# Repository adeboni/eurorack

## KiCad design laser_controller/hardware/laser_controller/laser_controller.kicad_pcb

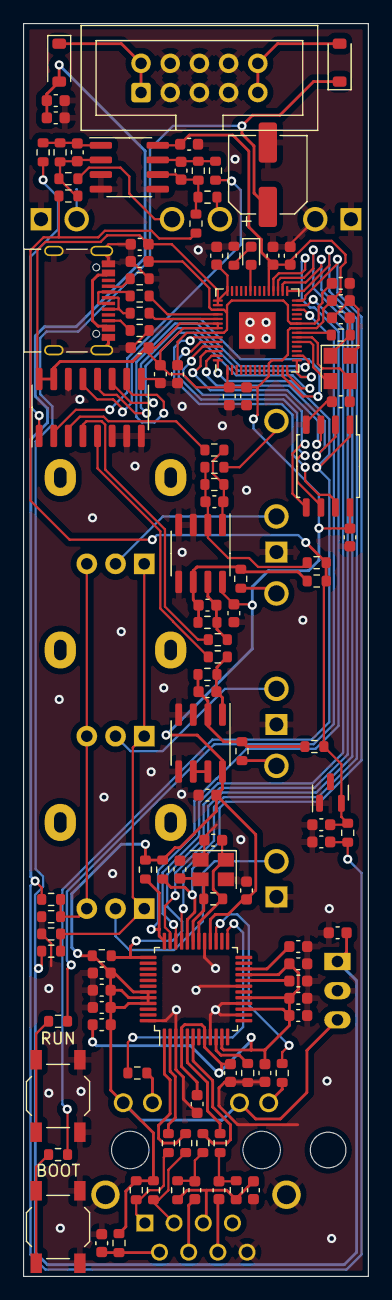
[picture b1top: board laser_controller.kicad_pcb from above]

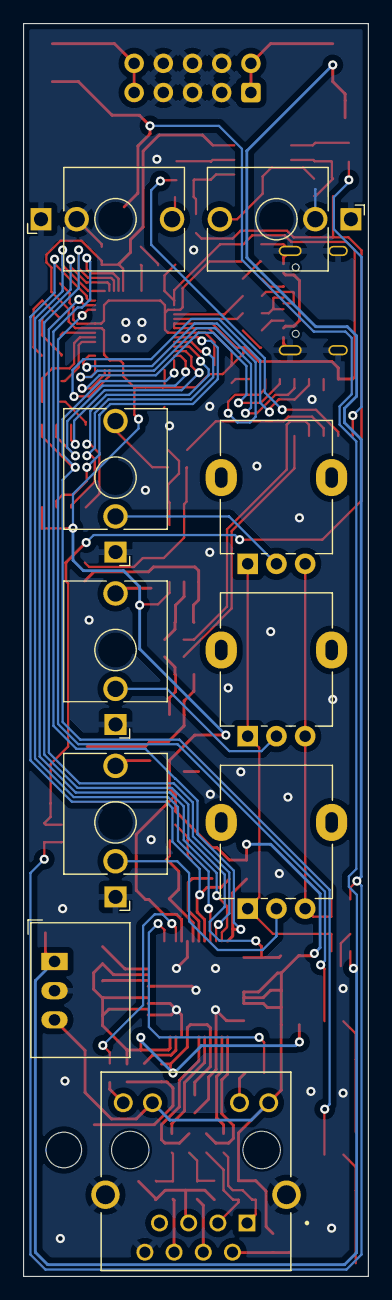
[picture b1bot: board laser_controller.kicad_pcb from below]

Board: 2 copper layers, 30.0 x 109.0 mm, 124 parts (10 on the bottom side), 87 nets.

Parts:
C1, C2, C3, C4, C5, C6, C7, C8, C9, C12, C13, C14, C15, C16, C17, C18, C19, C20, C21, C24, C29, C32, C33, C36, C37: 100n; C_0603_1608Metric
C10, C11, C47, C48: 1u; C_0603_1608Metric
C22, C25: 27p; C_0603_1608Metric
C23, C26: 18p; C_0603_1608Metric
C27: 4.7u; C_0603_1608Metric
C28: 22n; C_0603_1608Metric
C30, C31: 6.8n; C_0603_1608Metric
C34, C35, C44, C45: 10u; C_0603_1608Metric
C38, C39, C40, C41, C42: 470p; C_0603_1608Metric
C49: 100u; CP_Elec_6.3x5.4
D1: LED; LED_0603_1608Metric
D3, D5: SM4007; D_SOD-123
FB1: FerriteBead; L_0603_1608Metric
J1, J2, J3, J4, J5: AudioJack2_SwitchT; Jack_3.5mm_QingPu_WQP-PJ398SM_Vertical_CircularHoles
J6: Conn_02x05_Odd_Even; IDC-Header_2x05_P2.54mm_Vertical
J14: USB_C_Receptacle_USB2.0; USB_C_Receptacle_Palconn_UTC16-G
J16: SI-46001-F; BEL_SI-46001-F
R1, R4, R6, R7, R10, R11, R14, R15, R18, R19: 100k; R_0603_1608Metric
R2, R5, R9, R13, R17: 75k; R_0603_1608Metric
R3, R8, R12, R16, R20: 27k; R_0603_1608Metric
R21: 2k; R_0603_1608Metric
R22, R24, R52, R57, R59: 4.7k; R_0603_1608Metric
R23, R25: 3.3k; R_0603_1608Metric
R45, R46: 27; R_0603_1608Metric
R51, R54: 5.1k; R_0603_1608Metric
R53, R55, R56, R58: 4.7; R_0603_1608Metric
R60, R61, R62, R63: 49.9; R_0603_1608Metric
R68: 1M; R_0603_1608Metric
R69, R73, R77, R78: 1k; R_0603_1608Metric
R70, R71: 470; R_0603_1608Metric
R72: 10; R_0603_1608Metric
R74: 12.4k; R_0603_1608Metric
RV1, RV2, RV3: 1M; Potentiometer_Alpha_RD901F-40-00D_Single_Vertical
SW2, SW3: SW_Push; SW_SPST_TL3342
U1: MCP3208; SOIC-16_3.9x9.9mm_P1.27mm
U2, U3, U8: MCP6002-xSN; SOIC-8_3.9x4.9mm_P1.27mm
U4: RP2040; QFN-56-1EP_7x7mm_P0.4mm_EP3.2x3.2mm
U5: W5500; LQFP-48_7x7mm_P0.5mm
U7: W25Q128JVS; SOIC-8_5.23x5.23mm_P1.27mm
U9: LM4040-5V; SOT-23
U10: R-783.3-1.0; Converter_DCDC_RECOM_R-78E-0.5_THT
Y1: 12MHz; Crystal_SMD_3225-4Pin_3.2x2.5mm
Y2: 25MHz; Crystal_SMD_3225-4Pin_3.2x2.5mm

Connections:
+1V1: C1.1, C2.1, C10.1, U4.23 (DVDD), U4.45 (VREG_VOUT), U4.50 (DVDD)
+3.3V: C3.1, C4.1, C5.1, C6.1, C7.1, C8.1, C9.1, C11.1, C12.1, C13.1, C14.1, C15.1, C32.1, C33.1, C35.1, C36.1, C37.1, FB1.1, J16.10, J16.12, R52.1, R57.1, R59.1, R60.2, R61.2, R72.2, U1.15 (Vref), U1.16 (Vdd), U2.8 (V+), U3.8 (V+), U4.1 (IOVDD), U4.10 (IOVDD), U4.22 (IOVDD), U4.33 (IOVDD), U4.42 (IOVDD), U4.43 (ADC_AVDD), U4.44 (VREG_IN), U4.48 (USB_VDD), U4.49 (IOVDD), U5.28 (VDD), U5.43 (PMODE2), U5.44 (PMODE1), U5.45 (PMODE0), U7.8 (VCC), U8.8 (V+), U10.3 (OUT)
+3.3VA: C16.1, C17.1, C18.1, C19.1, C20.1, C21.1, FB1.2, U5.4 (AVDD), U5.8 (AVDD), U5.11 (AVDD), U5.15 (AVDD), U5.17 (AVDD), U5.21 (AVDD)
+12V: C34.1, C49.1, D3.1 (K), R22.1, U10.1 (IN)
-12V: C44.2, C45.2, C47.1, D5.2 (A), R21.1, R24.1
/CS_0: R52.2, U4.28 (GPIO17), U5.32 (~SCS)
/GPIO16: U4.27 (GPIO16), U5.34 (MISO)
/GPIO18: U4.29 (GPIO18), U5.33 (SCLK)
/GPIO19: U4.30 (GPIO19), U5.35 (MOSI)
/GPIO20: R59.2, U4.31 (GPIO20), U5.37 (~RST)
/GPIO21: R57.2, U4.32 (GPIO21), U5.36 (~INT)
/QSPI_SCLK: U4.52 (QSPI_SCLK), U7.6 (CLK)
/QSPI_SD0: U4.53 (QSPI_SD0), U7.5 (DI(IO0))
/QSPI_SD1: U4.55 (QSPI_SD1), U7.2 (DO(IO1))
/QSPI_SD2: U4.54 (QSPI_SD2), U7.3 (IO2)
/QSPI_SD3: U4.51 (QSPI_SD3), U7.7 (IO3)
/QSPI_SS: R78.1, U4.56 (QSPI_SS), U7.1 (~CS)
/RUN: R73.1, U4.26 (RUN)
/~USB_BOOT: R78.2, SW3.2
ACTn: R71.1, U5.27 (ACTLED)
CS_1: U1.10 (~CS/SHDN), U4.16 (GPIO13)
D+: J14.A6 (D+), J14.B6 (D+), R45.1
D-: J14.A7 (D-), J14.B7 (D-), R46.1
GND: C1.2, C2.2, C3.2, C4.2, C5.2, C6.2, C7.2, C8.2, C9.2, C10.2, C11.2, C12.2, C13.2, C14.2, C15.2, C16.2, C17.2, C18.2, C19.2, C20.2, C21.2, C22.2, C23.1, C24.1, C25.2, C26.2, C27.2, C28.1, C29.2, C32.2, C33.2, C34.2, C35.2, C36.2, C37.2, C44.1, C45.1, C47.2, C48.2, C49.2, J1.S, J1.TN, J2.S, J2.TN, J3.S, J4.S, J5.S, J6.3, J6.4, J6.5, J6.6, J6.7, J6.8, J14.A1 (GND), J14.A12 (GND), J14.B1 (GND), J14.B12 (GND), J14.S1 (SHIELD), J16.8, J16.SH, R23.2, R25.2, R51.1, R54.1, R74.1, R77.2, SW2.1, SW3.1, U1.6 (CH5), U1.7 (CH6), U1.8 (CH7), U1.9 (DGND), U1.14 (AGND), U2.3 (+), U2.4 (V-), U2.5 (+), U3.3 (+), U3.4 (V-), U3.5 (+), U4.19 (TESTEN), U4.57 (GND), U5.3 (AGND), U5.9 (AGND), U5.14 (AGND), U5.16 (AGND), U5.19 (AGND), U5.29 (GND), U5.48 (AGND), U7.4 (GND), U8.3 (+), U8.4 (V-), U8.5 (+), U9.1 (K), U10.2 (GND), Y1.2, Y1.4, Y2.2, Y2.4
LINKn: R70.1, U5.25 (LINKLED)
MISO_1: U1.12 (Dout), U4.15 (GPIO12)
MOSI_1: U1.11 (Din), U4.14 (GPIO11)
unnamed: C25.1, R69.2, Y1.1
unnamed: C38.1, R3.2, R4.1, U2.1
unnamed: C39.1, R6.1, R8.2, U2.7
unnamed: C40.1, R10.1, R12.2, U3.1
unnamed: C41.1, R14.1, R16.2, U3.7
unnamed: C42.1, R18.1, R20.2, U8.1
unnamed: D1.2 (A), U4.37 (GPIO25)
unnamed: D1.1 (K), R77.1
unnamed: D3.2 (A), J6.9, J6.10
unnamed: D5.1 (K), J6.1, J6.2
unnamed: J1.T, R1.1
unnamed: J2.T, R7.1
unnamed: J3.T, R19.1
unnamed: J3.TN, RV3.2
unnamed: J4.T, R11.1
unnamed: J4.TN, RV1.2
unnamed: J5.T, R15.1
unnamed: J5.TN, RV2.2
unnamed: J14.A5 (CC1), R51.2
unnamed: J14.B5 (CC2), R54.2
unnamed: J14.A4 (VBUS), J14.A9 (VBUS), J14.B4 (VBUS), J14.B9 (VBUS)
unnamed: J16.9, R71.2
unnamed: J16.11, R70.2
unnamed: C30.2, J16.4 (RD+)
unnamed: C31.1, J16.6 (RD-)
unnamed: C28.2, J16.2 (TCT), R72.1
unnamed: R22.2, R23.1, RV1.1, RV2.1, RV3.1
unnamed: R24.2, R25.1, RV1.3, RV2.3, RV3.3
unnamed: R73.2, SW2.2
unnamed: R4.2, U1.1 (CH0)
unnamed: R6.2, U1.2 (CH1)
unnamed: R10.2, U1.3 (CH2)
unnamed: R14.2, U1.4 (CH3)
unnamed: R18.2, U1.5 (CH4)
unnamed: C38.2, R1.2, R2.1, R3.1, U2.2 (-)
unnamed: C39.2, R5.1, R7.2, R8.1, U2.6 (-)
unnamed: C40.2, R9.1, R11.2, R12.1, U3.2 (-)
unnamed: C41.2, R13.1, R15.2, R16.1, U3.6 (-)
unnamed: R46.2, U4.46 (USB_DM)
unnamed: R45.2, U4.47 (USB_DP)
unnamed: C22.1, U4.20 (XIN), Y1.3
unnamed: R69.1, U4.21 (XOUT)
unnamed: C29.1, U5.22 (1V2O)
unnamed: R74.2, U5.10 (EXRES1)
unnamed: R56.1, U5.5 (RXN)
unnamed: R58.2, U5.6 (RXP)
unnamed: C27.1, U5.20 (TOCAP)
unnamed: R53.1, U5.1 (TXN)
unnamed: R55.2, U5.2 (TXP)
unnamed: C23.2, R68.2, U5.30 (XI/CLKIN), Y2.1
unnamed: C26.1, R68.1, U5.31 (XO), Y2.3
unnamed: C42.2, R17.1, R19.2, R20.1, U8.2 (-)
unnamed: U8.6 (-), U8.7
RCT: C24.2, J16.5 (RCT), R62.2, R63.2
RXN: C31.2, R56.2, R62.1
RXP: C30.1, R58.1, R63.1
SCK_1: U1.13 (CLK), U4.13 (GPIO10)
TXN: J16.3 (TD-), R53.2, R60.1
TXP: J16.1 (TD+), R55.1, R61.1
VREF-5V: C48.1, R2.2, R5.2, R9.2, R13.2, R17.2, R21.2, U9.2 (A)

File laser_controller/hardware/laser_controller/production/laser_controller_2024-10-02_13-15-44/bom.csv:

Designator,Footprint,Quantity,Value,LCSC Part #
"C1, C12, C13, C14, C15, C16, C17, C18, C19, C2, C20, C21, C24, C29, C3, C32, C33, C36, C37, C4, C5, C6, C7, C8, C9",0603,25,100n,C14663
"C10, C11, C47, C48",0603,4,1u,C15849
"C22, C25",0603,2,27p,C107045
"C23, C26",0603,2,18p,C1647
C27,0603,1,4.7u,C19666
C28,0603,1,22n,C21122
"C30, C31",0603,2,6.8n,C1631
"C34, C35, C43, C44, C45, C46",0603,6,10u,C96446
"C38, C39, C40, C41, C42",0603,5,470p,C1620
D1,0603,1,LED,C2286
"D3, D5",D_SOD-123,2,SM4007,C64898
FB1,0603,1,FerriteBead,C1002
J14,USB_C_Receptacle_Palconn_UTC16-G,1,USB_C_Receptacle_USB2.0,C709357
"R1, R10, R11, R14, R15, R18, R19, R4, R6, R7",0603,10,100k,C25803
"R12, R16, R20, R3, R8",0603,5,27k,C22967
"R13, R17, R2, R5, R9",0603,5,75k,C23242
R21,0603,1,2k,C22975
"R22, R24, R52, R57, R59",0603,5,4.7k,C23162
"R23, R25",0603,2,3.3k,C22978
"R45, R46",0603,2,27,C25190
"R51, R54",0603,2,5.1k,C23186
"R53, R55, R56, R58",0603,4,4.7,C23164
"R60, R61, R62, R63",0603,4,49.9,C23185
R68,0603,1,1M,C22935
"R69, R73, R77, R78",0603,4,1k,C21190
"R70, R71",0603,2,470,C23179
R72,0603,1,10,C22859
R74,0603,1,12.4k,C22865
"SW2, SW3",SW_SPST_TL3342,2,SW_Push,C318884
U1,SOIC-16_3.9x9.9mm_P1.27mm,1,MCP3208,C16939
"U2, U3, U8",SOIC-8_3.9x4.9mm_P1.27mm,3,MCP6002-xSN,C7377
U4,QFN-56-1EP_7x7mm_P0.4mm_EP3.2x3.2mm,1,RP2040,C2040
U5,LQFP-48_7x7mm_P0.5mm,1,W5500,C32843
U7,SOIC-8_5.23x5.23mm_P1.27mm,1,W25Q128JVS,C97521
U9,SOT-23,1,LM4040-5V,C206488
Y1,Crystal_SMD_3225-4Pin_3.2x2.5mm,1,12MHz,C9002
Y2,Crystal_SMD_3225-4Pin_3.2x2.5mm,1,25MHz,C9006

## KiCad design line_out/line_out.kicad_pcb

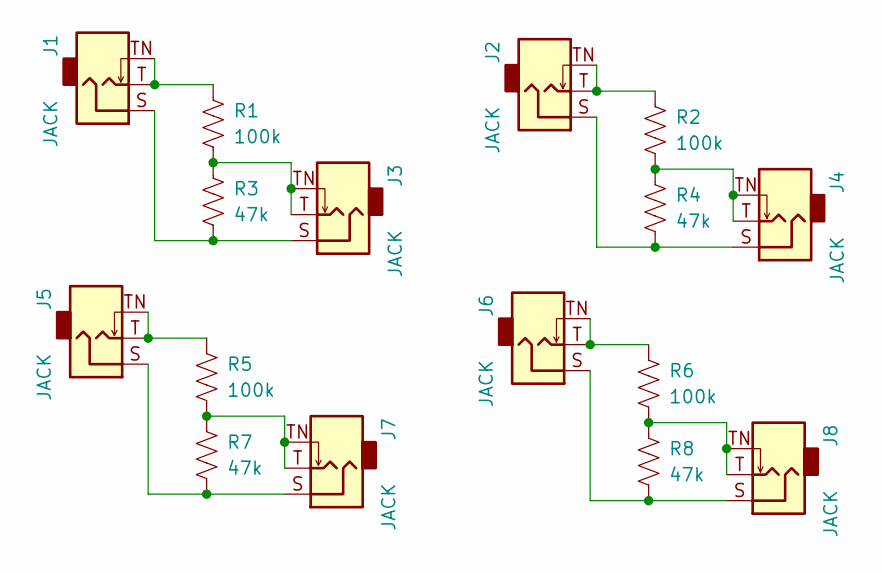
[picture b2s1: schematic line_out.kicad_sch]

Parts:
J1, J2, J3, J4, J5, J6, J7, J8: JACK; Jack_3.5mm_QingPu_WQP-PJ398SM_Vertical_CircularHoles
R1, R2, R5, R6: 100k; R_0603_1608Metric
R3, R4, R7, R8: 47k; R_0603_1608Metric

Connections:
unnamed: J1.S, J3.S, R3.2
unnamed: J1.T, J1.TN, R1.1
unnamed: J2.S, J4.S, R4.2
unnamed: J2.T, J2.TN, R2.1
unnamed: J3.T, J3.TN, R1.2, R3.1
unnamed: J4.T, J4.TN, R2.2, R4.1
unnamed: J5.S, J7.S, R7.2
unnamed: J5.T, J5.TN, R5.1
unnamed: J6.S, J8.S, R8.2
unnamed: J6.T, J6.TN, R6.1
unnamed: J7.T, J7.TN, R5.2, R7.1
unnamed: J8.T, J8.TN, R6.2, R8.1

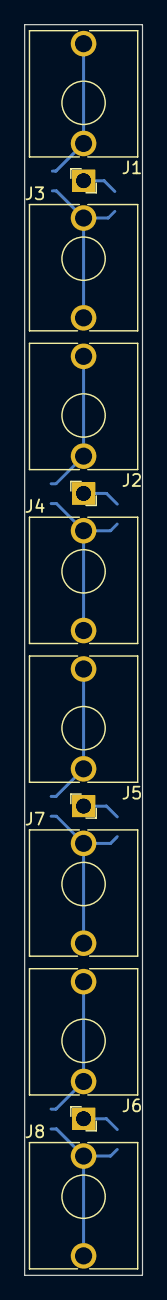
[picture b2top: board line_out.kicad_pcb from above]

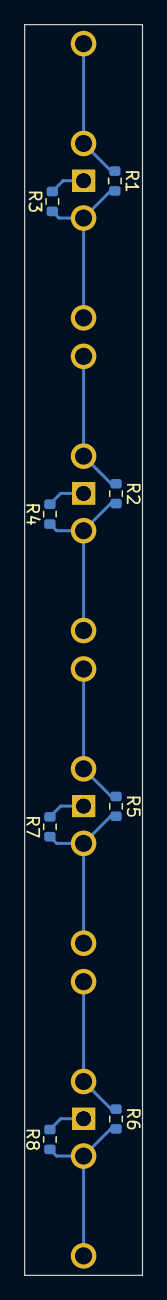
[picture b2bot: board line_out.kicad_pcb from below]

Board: 2 copper layers, 9.8 x 104.0 mm, 16 parts (8 on the bottom side), 12 nets.

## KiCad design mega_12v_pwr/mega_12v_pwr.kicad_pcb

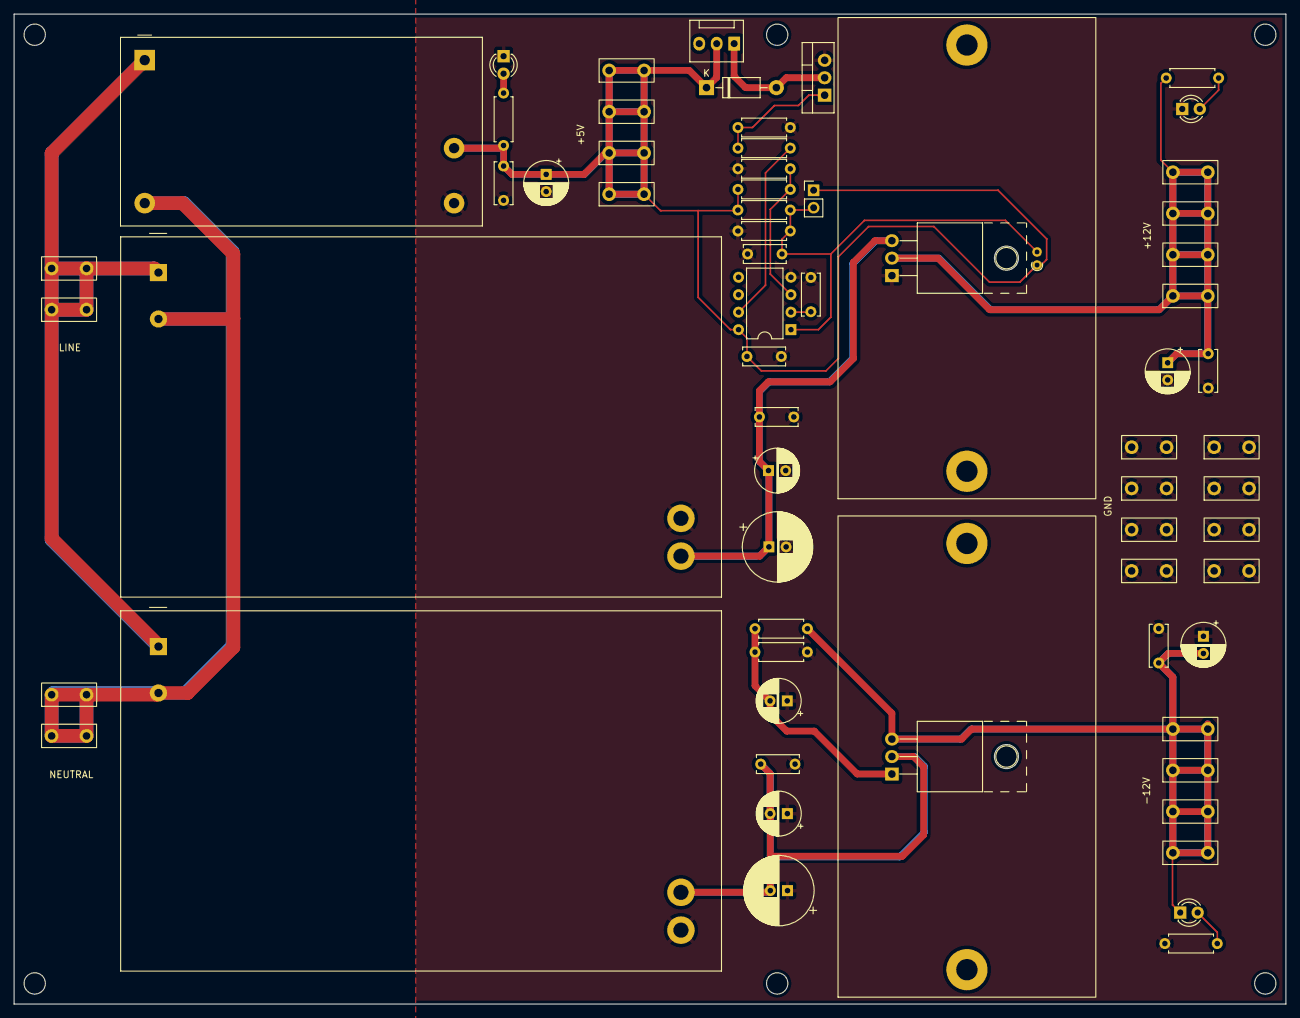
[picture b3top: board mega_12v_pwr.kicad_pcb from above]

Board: 2 copper layers, 185.0 x 144.0 mm, 67 parts (0 on the bottom side), 18 nets.

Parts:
C1, C2, C3, C4, C5, C8: 10u; CP_Radial_D6.3mm_P2.50mm
C6, C7: 100u; CP_Radial_D10.0mm_P2.50mm
C9, C10, C11, C12, C13, C14: 100n; C_Disc_D6.0mm_W2.5mm_P5.00mm
C15: 1u; C_Disc_D6.0mm_W2.5mm_P5.00mm
C17: 10n; C_Disc_D6.0mm_W2.5mm_P5.00mm
D1, D2, D3: LED; LED_D3.0mm
D4: 1N4007; D_DO-41_SOD81_P10.16mm_Horizontal
HS1, HS2: Heatsink; SK64
J1, J2, J3, J4, J5, J6, J7, J8, J9, J10, J11, J12, J13, J14, J15, J16, J17, J18, J19, J20, J22, J23, J24, J25: Conn_01x01; SPADE
J21: Conn_01x02; PinHeader_1x02_P2.54mm_Vertical
M1: Fan_PC_Chassis; FanPinHeader_1x03_P2.54mm_Vertical
PS1: IRM-20-5; Converter_ACDC_MeanWell_IRM-20-xx_THT
PS2, PS3: IRM-60-15; Converter_ACDC_MeanWell_IRM-60-xx_THT
Q2: IRLB8721PBF; TO-220-3_Vertical
R1: 390; R_Axial_DIN0207_L6.3mm_D2.5mm_P7.62mm_Horizontal
R2, R4: 4.7k; R_Axial_DIN0207_L6.3mm_D2.5mm_P7.62mm_Horizontal
R3: 2.2k; R_Axial_DIN0207_L6.3mm_D2.5mm_P7.62mm_Horizontal
R5: 3.3k; R_Axial_DIN0207_L6.3mm_D2.5mm_P7.62mm_Horizontal
R6: 2k; R_Axial_DIN0207_L6.3mm_D2.5mm_P7.62mm_Horizontal
R7, R11: 10k; R_Axial_DIN0207_L6.3mm_D2.5mm_P7.62mm_Horizontal
R8: 27k; R_Axial_DIN0207_L6.3mm_D2.5mm_P7.62mm_Horizontal
R9: 100; R_Axial_DIN0207_L6.3mm_D2.5mm_P7.62mm_Horizontal
R10: DNP; R_Axial_DIN0207_L6.3mm_D2.5mm_P7.62mm_Horizontal
TH1: 10k; R_Axial_DIN0204_L3.6mm_D1.6mm_P1.90mm_Vertical
U1: LT1084-12; TO-220-3_Horizontal_TabUp
U2: LT1033C; TO-220-3_Horizontal_TabUp
U4: DIP-8_W7.62mm

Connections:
+5V: C8.1, C9.1, C14.1, D4.1 (K), J15.1, J16.1, J17.1, J18.1, J21.1, M1.2 (+), PS1.4 (+Vo), R3.1, R8.1, R10.1, TH1.1, U4.8 (VDD)
+12V: C2.1, C10.1, J3.1, J4.1, J5.1, J6.1, R2.1, U1.2 (VO)
+15V: C1.1, C6.1, C11.1, PS2.3 (+Vout), U1.3 (VI)
-12V: C4.2, C13.2, D3.1 (K), J11.1, J12.1, J13.1, J14.1, R1.2, U2.3 (VO)
-15V: C3.2, C7.2, C12.2, PS3.4 (-Vout), U2.2 (VI)
GND: C1.2, C2.2, C3.1, C4.1, C5.1, C6.2, C7.1, C8.2, C9.2, C10.2, C11.2, C12.1, C13.1, C14.2, C15.2, C17.2, D1.1 (K), D2.1 (K), J7.1, J8.1, J9.1, J10.1, J22.1, J23.1, J24.1, J25.1, PS1.3 (-Vo), PS2.4 (-Vout), PS3.3 (+Vout), Q2.3 (S), R4.1, R5.1, R6.2, R7.2, R11.1, U1.1 (GND), U4.4 (GND)
LINE: J2.1, J20.1, PS1.1 (AC/L), PS2.1 (AC/L), PS3.1 (AC/L)
NEUT: J1.1, J19.1, PS1.2 (AC/N), PS2.2 (AC/N), PS3.2 (AC/N)
unnamed: D1.2 (A), R2.2
unnamed: D2.2 (A), R3.2
unnamed: D3.2 (A), R4.2
unnamed: D4.2 (A), M1.1 (-), Q2.2 (D)
unnamed: C17.1, J21.2, R6.1, R10.2, TH1.2, U4.1 (VIN)
unnamed: Q2.1 (G), R9.2, R11.2
unnamed: C5.2, R1.1, R5.2, U2.1 (ADJ)
unnamed: C15.1, U4.2 (CF)
unnamed: R7.1, R8.2, U4.3 (VAS)
unnamed: R9.1, U4.7 (VOUT)

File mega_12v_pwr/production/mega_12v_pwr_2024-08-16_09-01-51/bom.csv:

Designator,Footprint,Quantity,Value,LCSC Part #
"C1, C2, C3, C4, C5, C8",CP_Radial_D6.3mm_P2.50mm,6,10u,
"C10, C11, C12, C13, C9",C_Disc_D6.0mm_W2.5mm_P5.00mm,5,100n,
"C6, C7",CP_Radial_D10.0mm_P2.50mm,2,100u,
"D1, D2, D3",LED_D3.0mm,3,LED,
"HS1, HS2",SK64,2,Heatsink,
"J1, J10, J11, J12, J13, J14, J15, J16, J17, J18, J19, J2, J20, J3, J4, J5, J6, J7, J8, J9",SPADE,20,Conn_01x01,
PS1,Converter_ACDC_MeanWell_IRM-20-xx_THT,1,IRM-20-5,
"PS2, PS3",Converter_ACDC_MeanWell_IRM-60-xx_THT,2,IRM-60-15,
R1,R_Axial_DIN0207_L6.3mm_D2.5mm_P7.62mm_Horizontal,1,120,
"R2, R4",R_Axial_DIN0207_L6.3mm_D2.5mm_P7.62mm_Horizontal,2,2.2k,
R3,R_Axial_DIN0207_L6.3mm_D2.5mm_P7.62mm_Horizontal,1,1k,
R5,R_Axial_DIN0207_L6.3mm_D2.5mm_P7.62mm_Horizontal,1,860,
U1,TO-220-3_Horizontal_TabUp,1,LT1084-12,
U2,TO-220-3_Horizontal_TabUp,1,LT1033C,

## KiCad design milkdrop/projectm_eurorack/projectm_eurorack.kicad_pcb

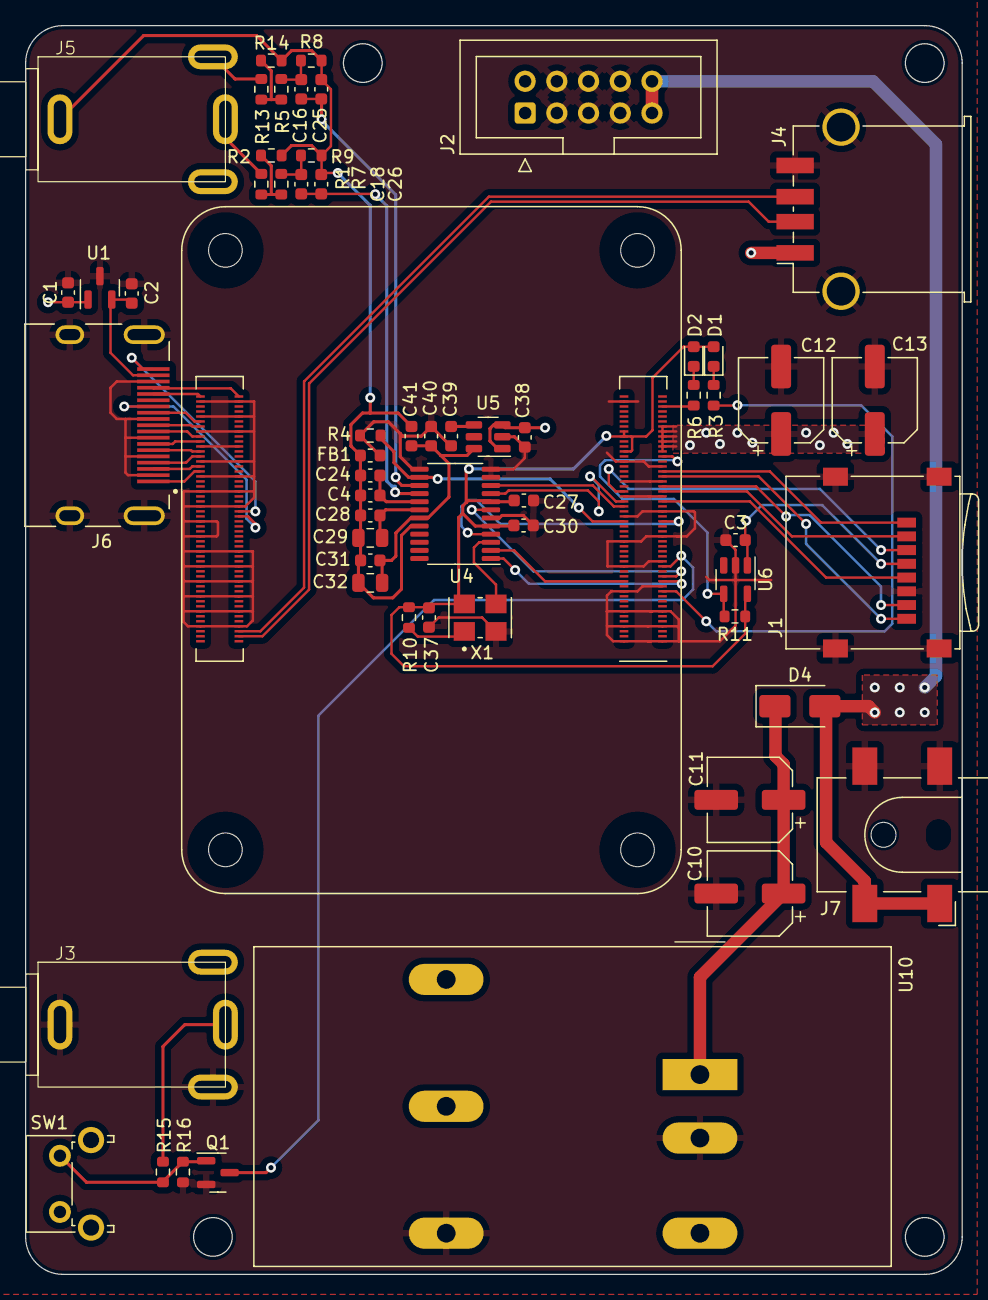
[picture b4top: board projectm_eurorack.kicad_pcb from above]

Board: 2 copper layers, 75.0 x 100.0 mm, 59 parts (0 on the bottom side), 57 nets.

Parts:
C1, C2, C4, C28, C30, C31, C38, C41: 100n; C_0603_1608Metric
C3, C16, C18, C24, C27, C40: 10u; C_0603_1608Metric
C10, C11, C12, C13: 100u; CP_Elec_6.3x5.8
C25, C26: 220p; C_0603_1608Metric
C29, C32: 47u; C_0805_2012Metric
C37, C39: 10n; C_0603_1608Metric
D1: LED Green; LED_0603_1608Metric
D2: LED Red; LED_0603_1608Metric
D4: SS54; D_SMA
FB1: FerriteBead_Small; L_0603_1608Metric
J1: Micro_SD_Card; microSD_HC_Wuerth_693072010801
J2: Conn_02x05_Odd_Even; IDC-Header_2x05_P2.54mm_Vertical
J3, J5: AudioJack3_SwitchT; 729JH
J4: USB_A; USB_A_TE_292303-7_Horizontal
J6: 690-019-298-412; EDAC 690-019-298-412
J7: Barrel_Jack_Switch; BarrelJack_CLIFF_FC681465S_SMT_Horizontal
Module1: ComputeModule4; Raspberry-Pi-4-Compute-Module
Q1: MMBT3904; SOT-23
R1, R13: 0; R_0603_1608Metric
R2, R14: nf; R_0603_1608Metric
R3, R6: 1k; R_0603_1608Metric
R4, R8, R9, R10: 10k; R_0603_1608Metric
R5, R7: 4.99k; R_0603_1608Metric
R11: 12K 1%; R_0603_1608Metric
R15: 100k; R_0603_1608Metric
R16: 33k; R_0603_1608Metric
SW1: SW_Push; SW_Tactile_SPST_Angled_PTS645Vx83-2LFS
U1: RT9742SNGV; SOT-23
U4: CS4270; TSSOP-24_4.4x7.8mm_P0.65mm
U5: TPS79301-EP; SOT-23-6
U6: RT9742GGJ5; SOT-23-5
U10: TEN20-2411WIN; Converter_DCDC_TRACO_TEN20-xxxx_THT
X1: 12.288MHz; XTAL_ASFL1-8.000MHZ-EC-T

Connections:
+5VA: C31.1, C32.1, C40.1, C41.1, U4.19 (VA), U5.6 (OUT)
/+3.3v: C27.1, C30.1, C37.1, D1.2 (A), D2.2 (A), Module1.78 (GPIO_VREF(1.8v/3.3v_Input)), Module1.84 (+3.3v_(Output)), Module1.86 (+3.3v_(Output)), R10.1, R11.1, U4.5 (VD), U4.8 (VLC), U6.5 (IN), X1.4 (Vdd)
/+5v: C1.1, C12.1, C13.1, C38.1, J4.1 (VBUS), Module1.77 (+5v_(Input)), Module1.79 (+5v_(Input)), Module1.81 (+5v_(Input)), Module1.83 (+5v_(Input)), Module1.85 (+5v_(Input)), Module1.87 (+5v_(Input)), SW1.1, U1.1 (IN), U5.1 (IN), U5.3 (EN), U10.3 (VOUT+)
/+12v: C10.1, C11.1, D4.1 (K), U10.1 (VIN+)
/HDMI0_CEC: J6.13 (CEC), Module1.151 (HDMI0_CEC)
/HDMI0_CK_N: J6.12 (CK-), Module1.190 (HDMI0_CLK_N)
/HDMI0_CK_P: J6.10 (CK+), Module1.188 (HDMI0_CLK_P)
/HDMI0_D0_N: J6.9 (D0-), Module1.184 (HDMI0_TX0_N)
/HDMI0_D0_P: J6.7 (D0+), Module1.182 (HDMI0_TX0_P)
/HDMI0_D1_N: J6.6 (D1-), Module1.178 (HDMI0_TX1_N)
/HDMI0_D1_P: J6.4 (D1+), Module1.176 (HDMI0_TX1_P)
/HDMI0_D2_N: J6.3 (D2-), Module1.172 (HDMI0_TX2_N)
/HDMI0_D2_P: J6.1 (D2+), Module1.170 (HDMI0_TX2_P)
/HDMI0_HOTPLUG: J6.19 (HPD/HEAC-), Module1.153 (HDMI0_HOTPLUG)
/HDMI0_SCL: J6.15 (SCL), Module1.200 (HDMI0_SCL)
/HDMI0_SDA: J6.16 (SDA), Module1.199 (HDMI0_SDA)
/HDMI_5v: C2.1, J6.18 (+5V), U1.2 (OUT)
/SD_CLK: J1.5 (CLK), Module1.57 (SD_CLK)
/SD_CMD: J1.3 (CMD), Module1.62 (SD_CMD)
/SD_DAT0: J1.7 (DAT0), Module1.63 (SD_DAT0)
/SD_DAT1: J1.8 (DAT1), Module1.67 (SD_DAT1)
/SD_DAT2: J1.1 (DAT2), Module1.69 (SD_DAT2)
/SD_DAT3: J1.2 (DAT3/CD), Module1.61 (SD_DAT3)
/SD_PWR: C3.1, J1.4 (VDD), U6.1 (OUT)
/SD_PWR_ON: Module1.75 (SD_PWR_ON), R11.2, U6.4 (EN)
/USBD_N: J4.2 (D-), Module1.103 (USB2_N)
/USBD_P: J4.3 (D+), Module1.105 (USB2_P)
/nPWR_LED: Module1.95 (nPI_LED_PWR), R6.2
GND: C1.2, C2.2, C3.2, C10.2, C11.2, C12.2, C13.2, C27.2, C30.2, C37.2, C38.2, C39.2, C40.2, FB1.2, J1.6 (VSS), J1.9 (SHIELD), J2.3, J2.4, J2.5, J2.6, J2.7, J2.8, J3.S, J3.TN, J4.4 (GND), J4.5 (Shield), J6.2 (D2S), J6.5 (D1S), J6.8 (D0S), J6.11 (CKS), J6.17 (GND), J6.SH1 (SH), J6.SH2 (SH), J6.SH3 (SH), J6.SH4 (SH), J7.2, J7.3, Module1.1 (GND), Module1.2 (GND), Module1.7 (GND), Module1.8 (GND), Module1.13 (GND), Module1.14 (GND), Module1.22 (GND), Module1.23 (GND), Module1.32 (GND), Module1.33 (GND), Module1.42 (GND), Module1.43 (GND), Module1.52 (GND), Module1.53 (GND), Module1.59 (GND), Module1.60 (GND), Module1.65 (GND), Module1.66 (GND), Module1.71 (GND), Module1.74 (GND), Module1.98 (GND), Module1.107 (GND), Module1.108 (GND), Module1.113 (GND), Module1.114 (GND), Module1.119 (GND), Module1.120 (GND), Module1.125 (GND), Module1.126 (GND), Module1.131 (GND), Module1.132 (GND), Module1.137 (GND), Module1.138 (GND), Module1.144 (GND), Module1.150 (GND), Module1.155 (GND), Module1.156 (GND), Module1.161 (GND), Module1.162 (GND), Module1.167 (GND), Module1.168 (GND), Module1.173 (GND), Module1.174 (GND), Module1.179 (GND), Module1.180 (GND), Module1.185 (GND), Module1.186 (GND), Module1.191 (GND), Module1.192 (GND), Module1.197 (GND), Module1.198 (GND), Q1.2 (E), R4.1, R16.1, U1.3 (GND), U4.6 (DGND), U4.11 (AD0/~CS/I2S/~LJ), U4.12 (AD1/CDIN/MDIV1), U4.13 (AD2/MDIV2), U5.2 (GND), U6.2 (GND), U10.2 (VIN-), U10.5 (VOUT-), X1.2 (GND)
GNDA: C4.2, C24.2, C25.1, C26.1, C28.2, C29.2, C31.2, C32.2, C41.2, FB1.1, J5.S, R2.2, R8.2, R9.2, R14.2, U4.20 (AGND)
GPIO12: Module1.31 (GPIO12), Q1.3 (C)
INA: C16.2, C25.2, U4.15 (AINA)
INB: C18.2, C26.2, U4.16 (AINB)
LRCLK: Module1.26 (GPIO19), U4.2 (LRCLK)
MCLK: U4.3 (MCLK), X1.3 (OUT)
unnamed: C16.1, R5.1, R8.1
unnamed: C18.1, R7.1, R9.1
unnamed: D1.1 (K), R3.1
unnamed: D2.1 (K), R6.1
unnamed: D4.2 (A), J2.9, J2.10, J7.1
unnamed: J3.T, R15.2
unnamed: J5.R, R13.2
unnamed: J5.T, R1.2
unnamed: Module1.21 (PI_nLED_Activity), R3.2
unnamed: Q1.1 (B), R15.1, R16.2, SW1.2
unnamed: R1.1, R2.1, R7.2
unnamed: R5.2, R13.1, R14.1
unnamed: C28.1, C29.1, U4.18 (FIL+)
unnamed: C4.1, C24.1, U4.17 (VQ)
unnamed: C39.1, U5.4 (BP)
unnamed: R10.2, X1.1 (EN)
R_CODEC: Module1.50 (GPIO17), R4.2, U4.14 (~RST)
SCLK: Module1.49 (GPIO18), U4.4 (SCLK)
SCL_CODEC: Module1.56 (GPIO3), U4.10 (SCL/CCLK/M0)
SDA_CODEC: Module1.58 (GPIO2), U4.9 (SDA/CDOUT/M1)
SDIN: Module1.25 (GPIO21), U4.1 (SDIN)
SDOUT: Module1.27 (GPIO20), U4.7 (SDOUT)

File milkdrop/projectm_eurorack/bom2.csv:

Comment,Designator,Footprint,LCSC Part Number
47u,"C29,C32",C_0805_2012Metric,C16780
SS54,D4,D_SMA,C22452
5.1k,R15,R_0603_1608Metric,C23186
1k,"R3,R6",R_0603_1608Metric,C21190
100n,"C41,C1,C4,C28,C38,C30,C2,C31",C_0603_1608Metric,C14663
12.288MHz,X1,XTAL_ASFL1-8.000MHZ-EC-T,C276419
10k,"R8,R16,R4,R10,R9",R_0603_1608Metric,C25804
100u,"C10,C12,C11,C13",CP_Elec_6.3x5.8,C180946
Micro_SD_Card,J1,microSD_HC_Wuerth_693072010801,C883270
CS4270,U4,TSSOP-24_4.4x7.8mm_P0.65mm,C1521475
12K 1%,R11,R_0603_1608Metric,C22790
10u,"C16,C40,C3,C27,C24,C18",C_0603_1608Metric,C96446
0,"R1,R13",R_0603_1608Metric,C21189
4.99k,"R5,R7",R_0603_1608Metric,C23046
FerriteBead_Small,FB1,L_0603_1608Metric,C1002
RT9742SNGV,U1,SOT-23,C3235509
10n,"C37,C39",C_0603_1608Metric,C57112
RT9742GGJ5,U6,SOT-23-5,C250547
220p,"C26,C25",C_0603_1608Metric,C1603
TPS79301-EP,U5,SOT-23-6,C2869546
LED Red,D2,LED_0603_1608Metric,C2286
Barrel_Jack_Switch,J7,BarrelJack_CLIFF_FC681465S_SMT_Horizontal,C431534
USB_A,J4,USB_A_TE_292303-7_Horizontal,C2763367
690-019-298-412,J6,EDAC 690-019-298-412,C138388
LED Green,D1,LED_0603_1608Metric,C72043
HIROSE DF40HC(3.0)-100DS-0.4V,"J100,J101",HIROSE DF40HC(3.0)-100DS-0.4V,C424649
